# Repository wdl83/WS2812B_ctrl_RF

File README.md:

# WS2812B Controller with nRF24L01+ 

## author:
Wlodzimierz Lipert https://github.com/wdl83

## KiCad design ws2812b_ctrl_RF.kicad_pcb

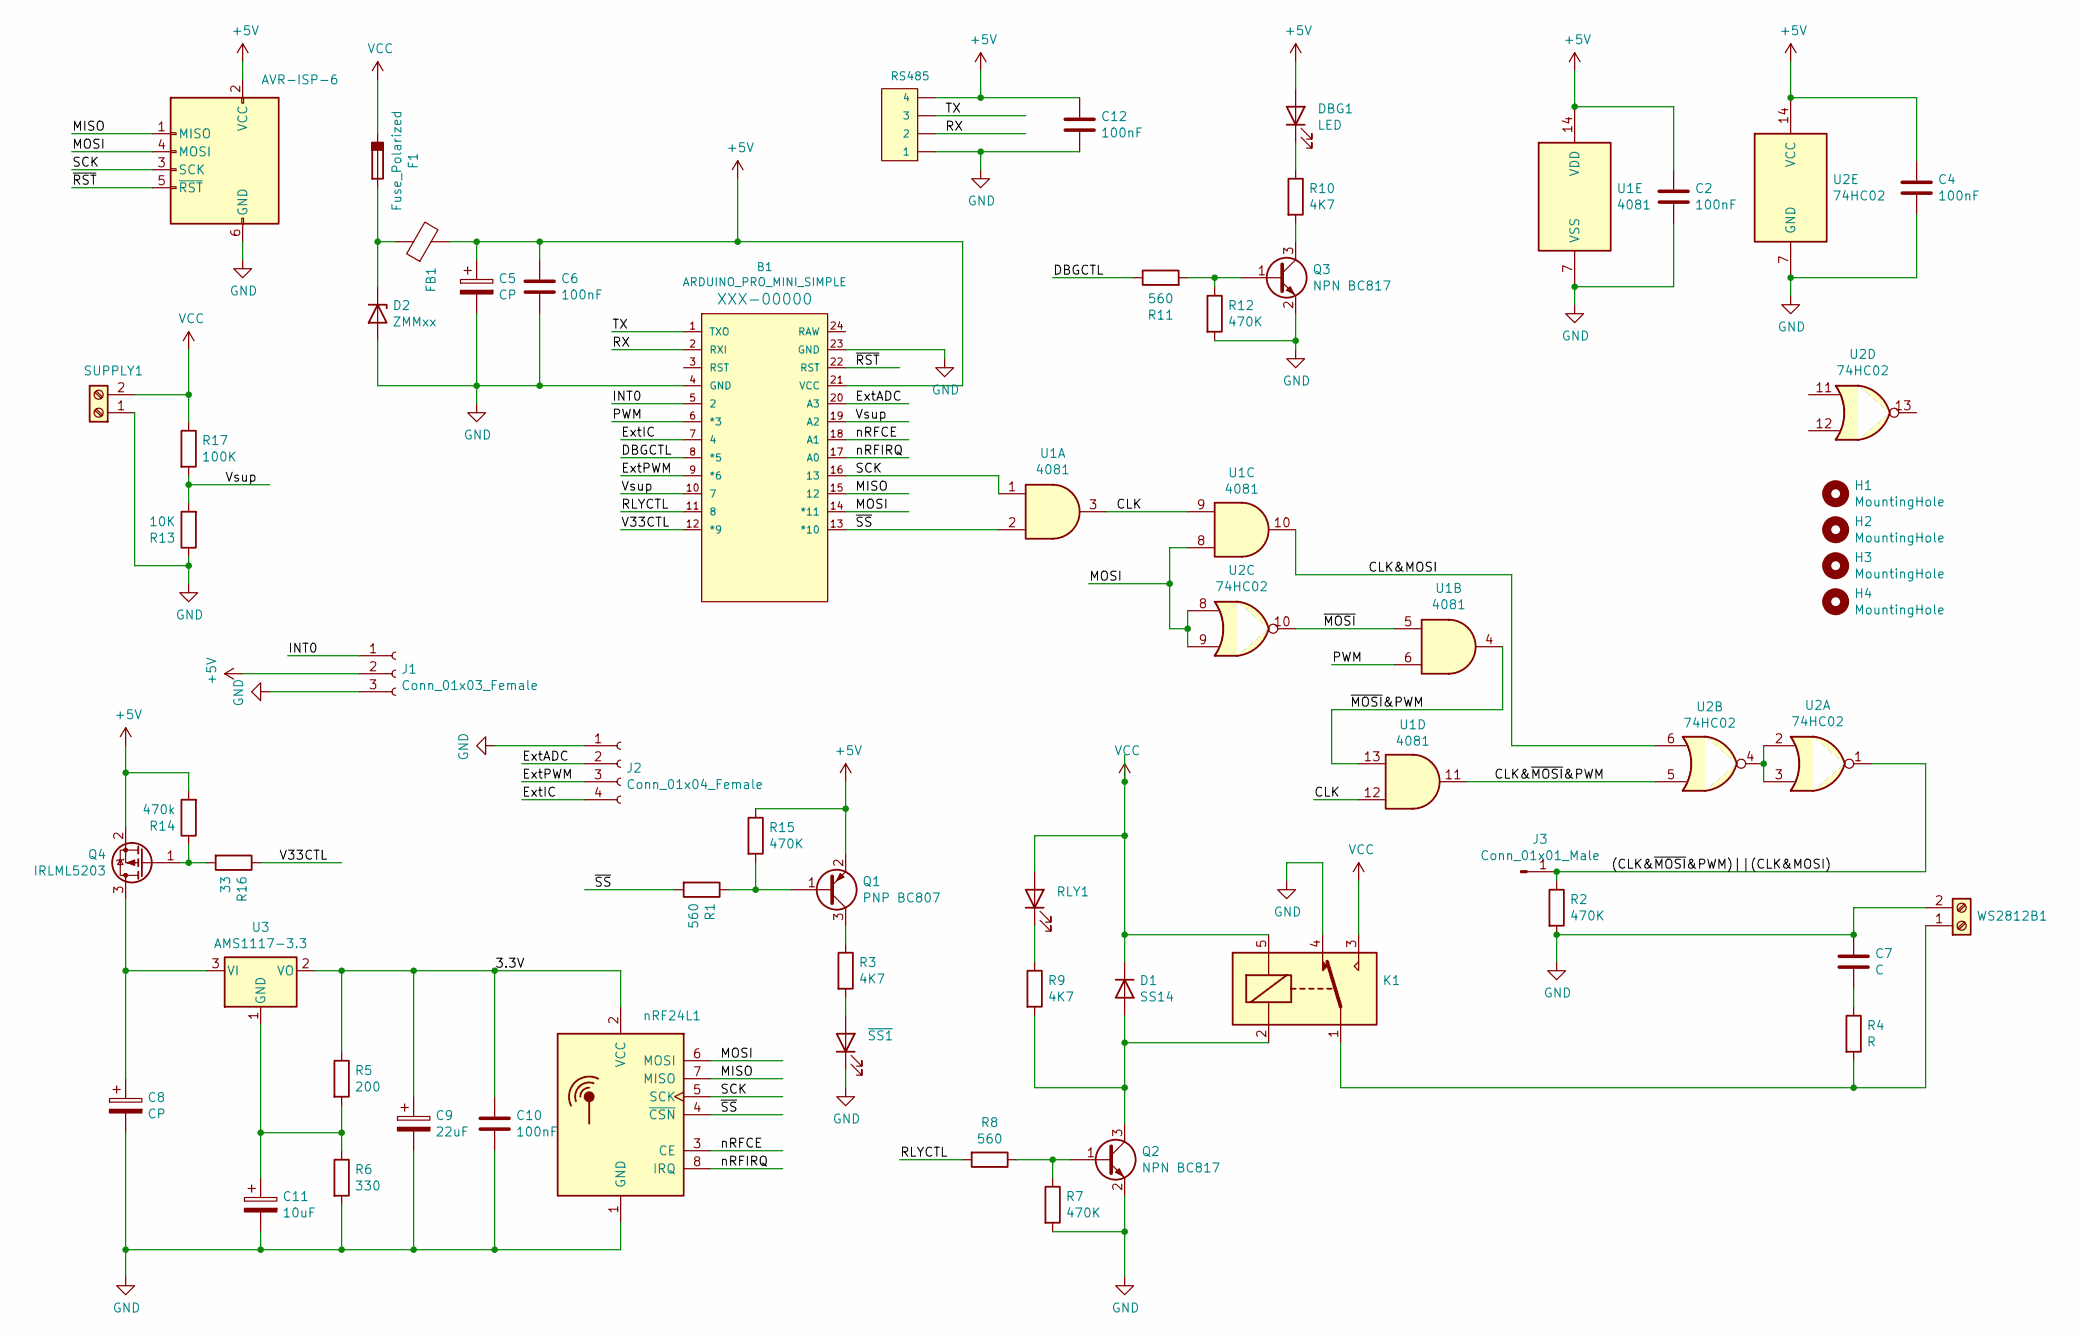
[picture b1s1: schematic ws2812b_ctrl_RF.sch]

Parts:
B1: ARDUINO_PRO_MINI_SIMPLE; ARDUINO_PRO_MINI
C2, C4, C6, C10, C12: 100nF; 1206
C5, C8: CP; CP_EIA-3528-21_Kemet-B_Pad1.50x2.35mm_HandSolder
C7: C; 1206
C9: 22uF; CP_EIA-3528-21_Kemet-B_Pad1.50x2.35mm_HandSolder
C11: 10uF; CP_EIA-3528-21_Kemet-B_Pad1.50x2.35mm_HandSolder
D1: SS14; D_SMA
D2: ZMMxx; D_MiniMELF_Handsoldering
DBG1: LED; LED_1206_3216Metric
F1: Fuse_Polarized; Fuse_1812_4532Metric_Pad1.30x3.40mm_HandSolder
FB1: Ferrite_Bead; L_1210_3225Metric
H1, H2, H3, H4: MountingHole; MountingHole_3.2mm_M3_ISO7380_Pad_TopBottom
ISP1: AVR-ISP-6; IDC-Header_2x03_P2.54mm_Vertical
J1: Conn_01x03_Female; JST_XH_B3B-XH-A_1x03_P2.50mm_Vertical
J2: Conn_01x04_Female; JST_XH_B4B-XH-A_1x04_P2.50mm_Vertical
J3: Conn_01x01_Male; Pin_D1.0mm_L10.0mm
K1: SANYOU_SRD_Form_C; Relay_SPDT_SANYOU_SRD_Series_Form_C
Q1: PNP BC807; SOT-23
Q2, Q3: NPN BC817; SOT-23
Q4: IRLML5203; SOT-23
R1, R8, R11: 560; 0805
R2, R7, R12, R15: 470K; 0805
R3, R9, R10: 4K7; 0805
R4: R; 0805
R5: 200; 0805
R6: 330; 0805
R13: 10K; 0805
R14: 470k; 0805
R16: 33; 0805
R17: 100K; 0805
RLY1: LED; LED_1206_3216Metric
RS485: CONN_04; 1X04
SUPPLY1: Screw_Terminal_01x02; TerminalBlock_bornier-2_P5.08mm
U1: 4081; SO-14_3.9x8.65mm_P1.27mm
U2: 74HC02; SO-14_3.9x8.65mm_P1.27mm
U3: AMS1117-3.3; SOT-223-3_TabPin2
WS2812B1: Screw_Terminal_01x02; TerminalBlock_bornier-2_P5.08mm
nRF24L1: NRF24L01_Breakout; nRF24L01_Breakout
~SS1: LED; LED_1206_3216Metric

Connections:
+5V: B1.21 (VCC), C2.1, C4.1, C5.1, C6.1, C12.1, DBG1.2 (A), FB1.2, ISP1.2 (VCC), J1.2, Q1.2 (E), Q4.2 (S), R14.2, R15.1, RS485.4, U1.14 (VDD), U2.14 (VCC)
/3.3V: C9.1, C10.1, R5.1, U3.2 (VO), nRF24L1.2 (VCC)
/(CLK&~MOSI~&PWM)||(CLK&MOSI): J3.1, R2.1, U2.1
/CLK: U1.3, U1.9, U1.12
/CLK&MOSI: U1.10, U2.6
/CLK&~MOSI~&PWM: U1.11, U2.5
/DBGCTL: B1.8 (*5), R11.1
/ExtADC: B1.20 (A3), J2.2
/ExtIC: B1.7 (4), J2.4
/ExtPWM: B1.9 (*6), J2.3
/INT0: B1.5 (2), J1.1
/MISO: B1.15 (12), ISP1.1 (MISO), nRF24L1.7 (MISO)
/MOSI: B1.14 (*11), ISP1.4 (MOSI), U1.8, U2.8, U2.9, nRF24L1.6 (MOSI)
/PWM: B1.6 (*3), U1.6
/RLYCTL: B1.11 (8), R8.2
/RX: B1.2 (RXI), RS485.2
/SCK: B1.16 (13), ISP1.3 (SCK), U1.1, nRF24L1.5 (SCK)
/TX: B1.1 (TXO), RS485.3
/V33CTL: B1.12 (*9), R16.1
/Vsup: B1.10 (7), B1.19 (A2), R13.2, R17.2
/nRFCE: B1.18 (A1), nRF24L1.3 (CE)
/nRFIRQ: B1.17 (A0), nRF24L1.8 (IRQ)
/~MOSI: U1.5, U2.10
/~MOSI~&PWM: U1.4, U1.13
/~RST: B1.22 (RST), ISP1.5 (~RST)
/~SS: B1.13 (*10), R1.2, U1.2, nRF24L1.4 (~CSN)
GND: B1.4 (GND), B1.23 (GND), C2.2, C4.2, C5.2, C6.2, C7.1, C8.2, C9.2, C10.2, C11.2, C12.2, D2.2 (A), ISP1.6 (GND), J1.3, J2.1, K1.4, Q2.2 (E), Q3.2 (E), R2.2, R6.2, R7.2, R12.2, R13.1, RS485.1, SUPPLY1.1, U1.7 (VSS), U2.7 (GND), WS2812B1.2, nRF24L1.1 (GND), ~SS1.1 (K)
unnamed: C7.2, R4.1
unnamed: C8.1, Q4.3 (D), U3.3 (VI)
unnamed: C11.1, R5.2, R6.1, U3.1 (GND)
unnamed: D1.2 (A), K1.2, Q2.3 (C), R9.2
unnamed: D2.1 (K), F1.2, FB1.1
unnamed: DBG1.1 (K), R10.1
unnamed: K1.1, R4.2, WS2812B1.1
unnamed: Q1.1 (B), R1.1, R15.2
unnamed: Q1.3 (C), R3.1
unnamed: Q2.1 (B), R7.1, R8.1
unnamed: Q3.1 (B), R11.2, R12.1
unnamed: Q3.3 (C), R10.2
unnamed: Q4.1 (G), R14.1, R16.2
unnamed: R3.2, ~SS1.2 (A)
unnamed: R9.1, RLY1.1 (K)
unnamed: U2.2, U2.3, U2.4
VCC: D1.1 (K), F1.1, K1.3, K1.5, R17.1, RLY1.2 (A), SUPPLY1.2

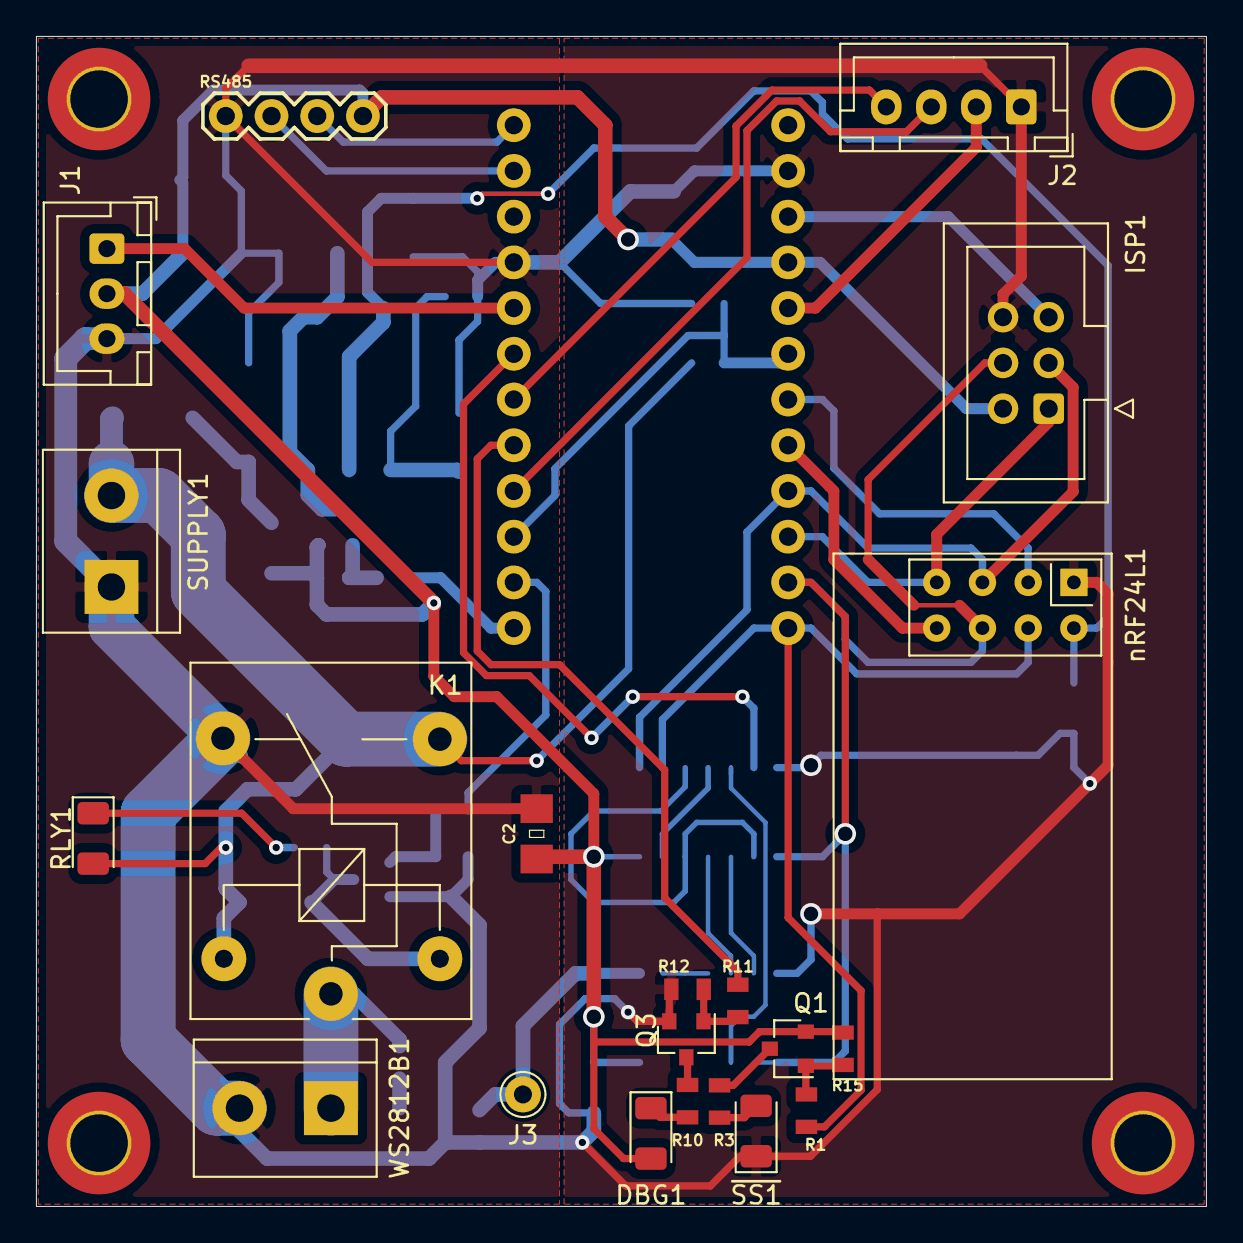
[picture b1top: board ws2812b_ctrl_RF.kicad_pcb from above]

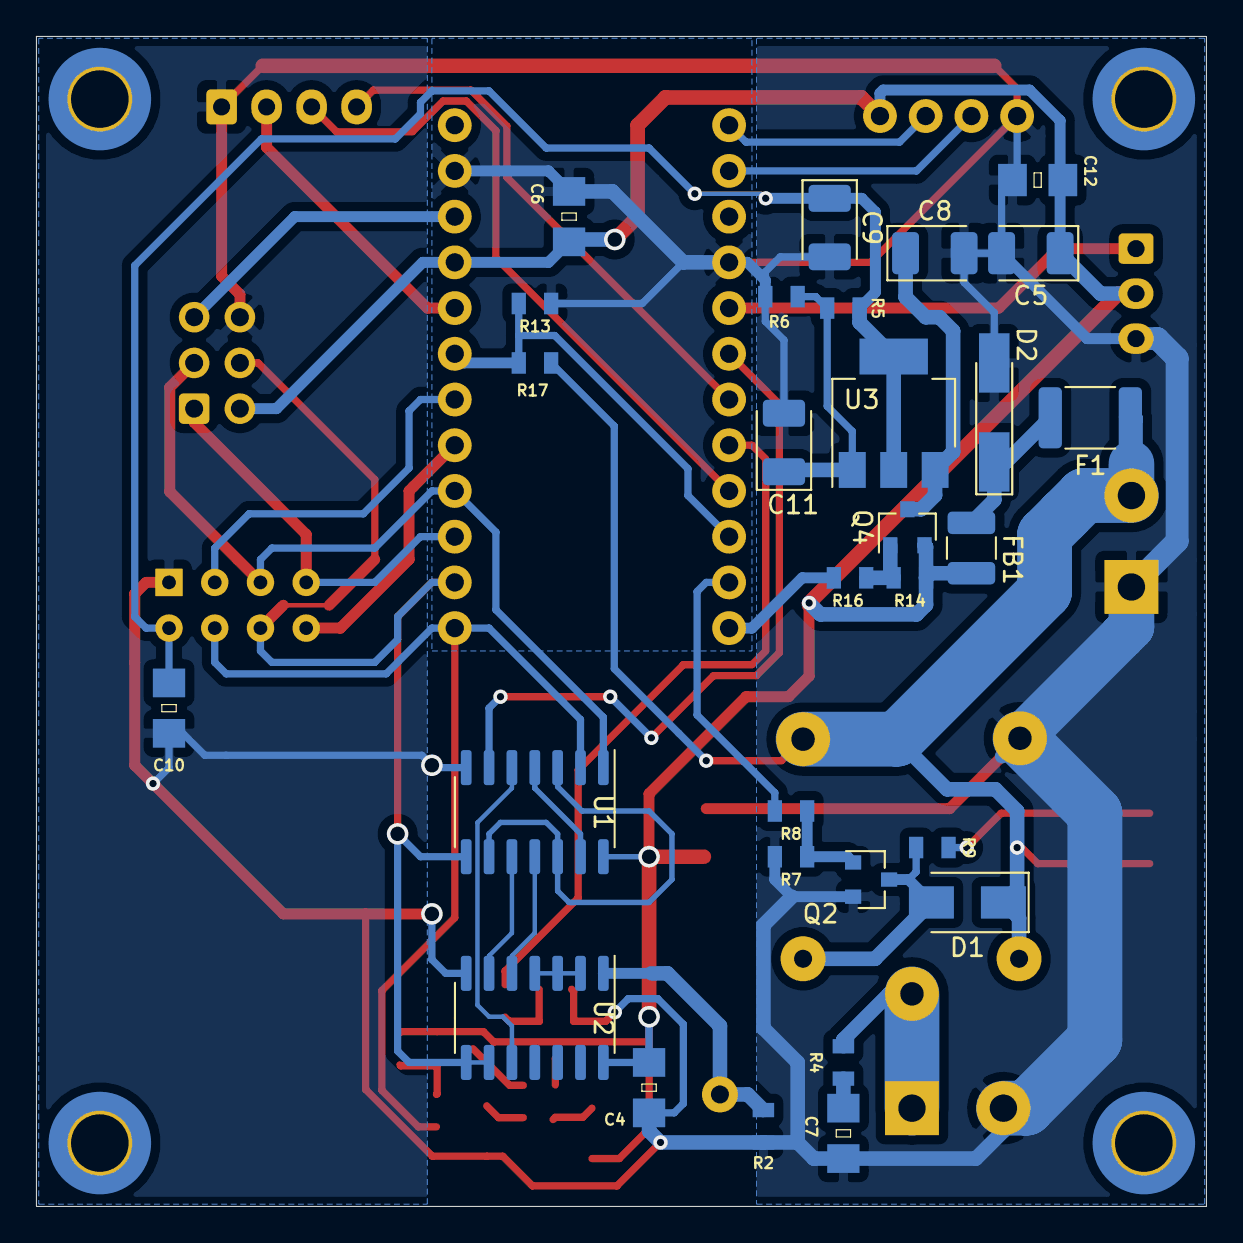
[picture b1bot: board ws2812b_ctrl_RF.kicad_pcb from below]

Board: 2 copper layers, 65.0 x 65.0 mm, 54 parts (29 on the bottom side), 43 nets.

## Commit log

2020-11-27 Version 1.
2021-08-27 Version 2.
2021-08-27 Added Version 2 info (PCB not verified yet).
2021-08-27 Added Version 2 top/bottom PCB.
2021-08-27 Fixed typo.
2021-12-05 Added HW v1 schematic and PCB layout images.
